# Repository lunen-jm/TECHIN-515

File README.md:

# GrainGuard Farm Monitoring System

A comprehensive farm monitoring system with IoT sensors, cloud backend, and web interface for tracking grain bin conditions. This project is built using ESP32-based sensors, Firebase, and React.

## Project Structure

- **`cloudApp/`** - Main web application built with React and Material-UI
  - Deploys to Netlify
  - Uses Firebase for data storage and authentication
  - Includes dashboard for farm sensor monitoring

- **`webApp/`** - Next-generation web interface (in development)
  - Uses modern UI components
  - Enhanced device provisioning

- **`arduinoProjects/`** - ESP32 sensor firmware
  - `wifi_provisioning/` - WiFi setup and device registration
  - `sensors/` - Sensor reading and data transmission
  - `localDisplay/` - Code for optional display modules

- **`firebase/`** - Firebase cloud functions and rules
  - Device registration APIs
  - Security rules
  - Background processing

- **`PCB/`** - Hardware design files for sensor modules
  - KiCad PCB designs
  - 3D printable enclosure files
  - Manufacturing exports

## Getting Started

### Web Application

The main web application is located in the `cloudApp` directory. See [cloudApp/README.md](cloudApp/README.md) for detailed setup instructions.

1. Navigate to the cloudApp directory:
   ```
   cd cloudApp
   npm install
   npm start
   ```

2. Configure Firebase:
   - Create `.env.local` from `.env.template`
   - Add your Firebase credentials

### Hardware Setup

For device setup instructions, see [WiFi_Provisioning_Implementation_README.md](WiFi_Provisioning_Implementation_README.md).

## Deployment

### Netlify Deployment

The web application is configured for deployment on Netlify:
- Build settings already configured in `netlify.toml`
- Environment variables must be manually set in Netlify dashboard
- Client-side routing configured with `_redirects` 

### Firebase Deployment

Cloud functions can be deployed with:
```
cd firebase/functions
npm install
firebase deploy --only functions
```

## Documentation

- [WiFi Provisioning Plan](WiFi_Provisioning_Plan.md) - Technical design for device setup
- [WiFi Provisioning Implementation](WiFi_Provisioning_Implementation_README.md) - Implementation details
- [Database Structure](DBStructure.md) - Firestore data model
- [Security Documentation](SECURITY.md) - Comprehensive security measures and incident response

## Security Notes

### 🔐 Important Security Update (December 2024)

**Incident Summary**: During development, a Firebase API key was temporarily exposed in the git repository. This issue has been completely resolved with the following actions:

1. **Immediate Response**:
   - The exposed API key was immediately invalidated and replaced
   - The `.env` file was removed from git tracking
   - `.gitignore` was updated to prevent future `.env` file commits

2. **Security Enhancements**:
   - **Firebase App Check** with reCAPTCHA v3 integration for additional protection
   - API key restrictions configured in Google Cloud Console
   - Comprehensive security audit completed

3. **Why Your Data Remains Secure**:
   - Firebase API keys are **not secret** - they identify your project but don't grant privileged access
   - **Firebase Security Rules** control all data access permissions
   - **App Check** prevents unauthorized app usage
   - The exposed key had **no write permissions** to sensitive data

### General Security Practices

- ⚠️ `.env` files should never be committed to the repository
- Firebase security rules should be tightened for production  
- Test credentials should be replaced for deployment
- Regular security audits are performed before major releases

## License

All rights reserved © 2025

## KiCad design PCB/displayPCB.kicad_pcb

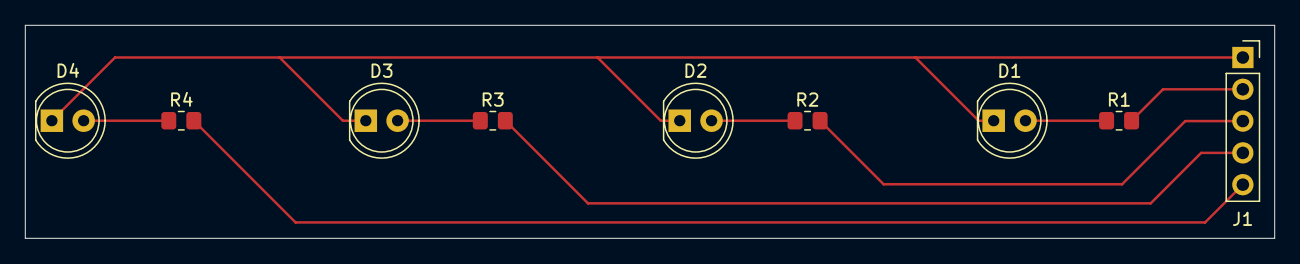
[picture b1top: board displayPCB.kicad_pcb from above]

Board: 2 copper layers, 99.8 x 17.0 mm, 9 parts (0 on the bottom side), 9 nets.

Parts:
D1: Blue LED; LED_D5.0mm
D2, D3, D4: Red LED; LED_D5.0mm
J1: Conn_01x05_Socket; PinSocket_1x05_P2.54mm_Vertical
R1, R2, R3, R4: R; R_0805_2012Metric_Pad1.20x1.40mm_HandSolder

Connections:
unnamed: D1.2 (A), R1.1
unnamed: D1.1 (K), D2.1 (K), D3.1 (K), D4.1 (K), J1.1
unnamed: D2.2 (A), R2.1
unnamed: D3.2 (A), R3.1
unnamed: D4.2 (A), R4.1
unnamed: J1.2, R1.2
unnamed: J1.3, R2.2
unnamed: J1.4, R3.2
unnamed: J1.5, R4.2

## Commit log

2025-04-01 Created initial repository structure
2025-05-06 INITIAL REACT APP
2025-05-06 updated packages, db
    - Updated packages, made them compatible and modernized a few for consistency.
    - Changed the site to more of a dashboard oriented layout
    - Created the initial DB schema, documentation, and DB structure (added in ERD for ease of creation too)
2025-05-07 write data into firebase
2025-05-13 database test
    database includes farm, users, devices and sensorreadings are all in different tables
    Interface that can show 2 devices and the sensorreading through API
2025-05-13 PCB & Enclosure Additions
2025-05-13 Remove sensitive credentials and update gitignore
2025-05-13 delete key
    delete key
2025-05-13 app update 1
    - reworked overall design
    - added new database schema
    - prepped for netlify deployment
    - created admin view & data feed
2025-05-13 quick app fix 1
    - fixed build errors from netlify
    - added .env file to not treat warnings as errors
    - fixed ESLint errors, removed unused imports and variables
2025-05-13 quick app fix 1 pt.2
    - additional changes saved
2025-05-13 quick fix 3
    - another linting issue
2025-05-13 authentication added
    - Created authentication system
    - Added in email / google SSO
    - Created production level sign-ons
    - Developed more profile options and management UI
2025-05-13 ESLint fix
2025-05-22 website update 1
    updated the website with a more streamlined design
2025-05-22 es lint hotfix
2025-05-22 es lint hotfix 2
2025-05-23 app update - login, style, bins
    - Added new styling to login page, followed designer ideas and added in a photo and general styling
    - Shifted the design to a more minimalist design rather than a google dashboard style
    - Started working on implementing tanks, made a showcase page
    - Started working on device pages, made a showcase page
2025-05-26 additional UI & initial device management
    - worked on device and farm page ui
    - added additional firebase functionalities
    - charts work on device pages now
    - firebase functions and device management back end is started
2025-05-26 quick fix
2025-05-26 RECAPTCHA & documentation
    - added recaptcha app check functionality
    - updated documentation (API was public, but no risk)
2025-05-26 farm update
    - added more farm functionality
    - changed farms page to get rid of some dashboard options
    - changed device page to show list of all devices user can access
    - continued adding documentation
2025-05-26 hotfix
    - error hotfixes for builf
2025-05-27 Dark mode & Alert Center
    - Added dark mode
    - Optimized dark mode, ensured proper implementation throughout app
    - Added alert center
    - Created user flow for alert management
    - Minor UI tweaks
2025-05-27 Update ThemeContext.tsx
    eslint fix
2025-05-29 Device Management Update
    - Worked on creating device registration workflow
    - Device management pages were fixed and enhanced
    - General UI fixes throughout the site
    - Device cards were updated to better represent data
2025-05-30 Registration Code Fix
    - Fixed registration code that prevented creation
    - Updated Firebase functions to better handle device registration
2025-06-02 Milestone 3 update
    - Updated UI
    - Work on user flows
2025-06-02 Auth Fix
    - Fixed authentication system
    - ReCAPTCHA Enterprise implementation
2025-06-02 auth hotfix
2025-06-02 recaptcha hotfix 2
2025-06-02 more auth fixes and firebase fixes
2025-06-02 auth hotfixes
    more
2025-06-03 cleanup
    quick cleanup for deployment
2025-06-03 recaptcha fix again
2025-06-03 Auth0 Implementation
2025-06-03 hotfix
2025-06-03 auth hf
2025-06-03 eslint hf
2025-06-03 fixes
    ai fixes and oversights
2025-06-03 Fix secrets scanning: Remove hardcoded AUTH0_AUDIENCE values and configure Netlify to omit AUTH0_AUDIENCE from scanning
2025-06-03 removed auth0
